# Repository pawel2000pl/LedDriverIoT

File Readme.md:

# IOT RGB Led driver

Project was designed for XIAO ESP32C3 and Waveshare ESP32C3-Zero.<br>
Compilable with Arduino and ESP-IDF.

## Example hardware application

## Screenshots

### Mobile

### Landscape (for computers)

### No-script (for bricks)

### Favorites

### Confguration

### Everything available also in dark-mode (auto detect)

## How to use a docker container
```
docker build -t led_driver_idf -f Idf.Dockerfile . && docker run -it -p 8000:8000 led_driver_idf
# or
# docker build -t led_driver_arduino -f Arduino.Dockerfile . && docker run -it -p 8000:8000 led_driver_arduino
```
then open http://0.0.0.0:8000 in your browser and download a binary file.

You can aslo run a script which builds the image, runs the container, downloads this file automatically and removes the container:
```
./compile_with_docker.sh
```

The file `iot-led-driver.bin` can be uploaded on `Configuration` page in `Update` tab.

## How to compile without a docker container

#### For all compilations
Before the compilation, it is required to compile resources to `.cpp` and `.h` files. It is also required after any modification of any file in the `resources` directory.
To compile resources, execute in the project directory:
~~~
python3 ./compilation_utils/compile_resources.py
~~~

#### For idf:
On the first usage of microcontroller you should run `idf.py erase_flash` to ensure that flash partitions will be initialized properly.<br>
Run `idf.py build` in the project directory.

#### For Arduino:
Open the file `main/main.ino` in Arduino. Set the following parameters:
* board: ESP32C3 - Dev module (requires additional installation)
* CPU Frequency: 160MHz (default)
* Flash size: 4MB
* Partition scheme: Minimal SPIFFS (1.9MB APP with OTA / 190kB SPIFFS)

## Runtime statistics
The runtime statistics are available on `/statistics.txt` endpoint.<br>
The last system statistics:
~~~
=== Tasks info ===
Name             |        Ticks | CPU % | Free stack |  Stack ptr
-----------------+--------------+-------+------------+------------
IDLE             |    390961538 |   85% |       1240 | 0x3fca6ef8
loopTask         |     34119316 |    7% |       3992 | 0x3fca87a8
knobs            |     20251982 |    4% |       1488 | 0x3fcb55d0
wifi             |      2405020 |    0% |       2128 | 0x3fcaedb0
tiT              |      1366588 |    0% |       2744 | 0x3fcaad80
animations       |       790686 |    0% |       1568 | 0x3fcb68a0
esp_timer        |       786223 |    0% |       3672 | 0x3fca4be8
shutdown         |       472535 |    0% |       1720 | 0x3fcb5f38
sys_evt          |         8169 |    0% |       2152 | 0x3fcac204
mdns             |         5225 |    0% |       3116 | 0x3fcb0fe4
arduino_events   |         4456 |    0% |       2836 | 0x3fcad03c
Tmr Svc          |            8 |    0% |       1792 | 0x3fca7660

=== Heap info ===
Total size:             247524
Minimum free heap:      111860  ( 45% )
Total free bytes:       155624  ( 62% )
Total allocated bytes:   91900  ( 37% )
Largest free block:     114688  ( 46% )
Blocks free:                10
Blocks allocated:          405
~~~

## How to connect for the first time

* Scan networks and find network with SSID `LedDriver` and connect to them with `ledDriver` password. Then type in browser `http://192.168.1.1`.
* If you do not see any network with SSID `LedDriver`, create it (as a Hotspot) on your phone with password `ledDriver` and restart the driver. The Hotspot must work with WiFi 5 or an older version.

Unfortunately, there is no way to predetermine driver's IP address in a network other than its own AccessPoint. <br>
The driver supports mDNS technology. After connecting to your network, try to enter the driver's hostname with suffix `.local` (f.e.: `http://led-driver.local`) in an address bar of a browser. Sometimes this technology requires a while to be detected by other devices in the network.<br>
In case of using `https` protocol you may be warned about danger of self signed or untrusted certificate.
Skip it and/or add this certificate to exceptions. 

## Hardware

### How it works

Select one of four possible configurations:
* Multiplexer #1
* Multiplexer #2
* Multiplexer #3
* simple #1
* simple #2
* unconnected

Each configuration might be modified by disconnecting potentiometers or removing thermistors.
The software matches pins automatically.

### Table with led driver pinout

...and possible hardware configurations

Pin|Name|XIAO|Waveshare|Multiplexer #1|Multiplexer #2|Multiplexer #3|Simple #1|Simple1 #2|Comment
---|----|----|---------|--------------|--------------|--------------|--------------|----------------|-------
1|LNA_IN|ANT|ANT|ANT|ANT|ANT|ANT|ANT|
2|VDD3P3|VCC 3,3|VCC 3,3|VCC 3,3|VCC 3,3|VCC 3,3|VCC 3,3|VCC 3,3|
3|VDD3P3|VCC 3,3|VCC 3,3||||||
4|XTAL_32K_P|internal|GP0||||||Cannot be connected during the booting (H/Z)
5|XTAL_32K_N|internal|GP1||||||Cannot be connected during the booting (H/Z)
6|GPIO2|D0|GP2|Mult COM|Mult COM|Mult COM|Potentiometer 0|Potentiometer 0|
7||EN|EN||||||
8|GPIO3|D1|GP3|H/Z|GND|UP|Potentiometer 1|Potentiometer 1|
9|MTMS|D2|GP4|FAN|FAN|FAN|Potentiometer 2|Potentiometer 2|
10|MTDI|D3|GP5|FLASH RST|FLASH RST|FLASH RST|FLASH RST|LED OUT 0|
11|VDD3P3_RTC|VCC 3,3|VCC 3,3||||||
12|MTCK|D4|GP6|Mult. SEL0|Mult. SEL0|Mult. SEL0|FAN (short them all)|LED OUT 1|
13|MTDO|D5|GP7|Mult. SEL1|Mult. SEL1|Mult. SEL1|FAN (short them all)|LED OUT 2|
14|GPIO8|D8|GP8|LED OUT 1|LED OUT 1|LED OUT 1|LED OUT 1|LED OUT 3|
15|GPIO9|D9|GP9|LED OUT 2|LED OUT 2|LED OUT 2|LED OUT 2|FLASH RST|Pulled-up during the booting (internal)
16|GPIO10|D10|GP10|LED OUT 3|LED OUT 3|LED OUT 3|LED OUT 3|FAN (short them all)|
17|VDD3P3_CPU|VCC 3,3|VCC 3,3||||||
18|VDD_SPI|VDD SPI|VDD SPI||||||
19|SPIHD|internal|internal||||||
20|SPIWP|internal|internal||||||
21|SPICS0|internal|internal||||||
22|SPICLK|internal|internal||||||
23|SPID|internal|internal||||||
24|SPIQ|internal|internal||||||
25|GPIO18|internal|ESP_USB_DP||||||
26|GPIO19|internal|ESP_USB_DM||||||
27|U0RXD|D7|GP20|LED OUT 0|LED OUT 0|LED OUT 0|LED OUT 0||
28|U0TXD|D6|GP21|Mult. SEL2|Mult. SEL2|Mult. SEL2|FAN (short them all)|FAN (short them all)|
29|XTAL_N|internal|internal||||||
30|XTAL_P|internal|internal||||||
31|VDDA|internal|internal||||||
32|VDDA|internal|internal||||||
33|GND|GND|GND||||||
Mult. Ch0||||Thermistor 0|Potentiometer 0|Thermistor 0|||
Mult. Ch1||||Thermistor 1|Potentiometer 1|Thermistor 1|||
Mult. Ch2||||Thermistor 2|Potentiometer 2|Thermistor 2|||
Mult. Ch3||||Thermistor 3|Potentiometer 3|Thermistor 3|||
Mult. Ch4||||Potentiometer 0|||||
Mult. Ch5||||Potentiometer 1|||||
Mult. Ch6||||Potentiometer 2|||||
Mult. Ch7||||Potentiometer 3|||||

### XIAO ESP32C3 board pinout - cheat sheet

### Waveshare ESP32C3-Zero board pinout - cheat sheet

### ESP32-C3 VROOM V2 pinout - cheat sheet

### ESP32-C3 pinout - cheat sheet

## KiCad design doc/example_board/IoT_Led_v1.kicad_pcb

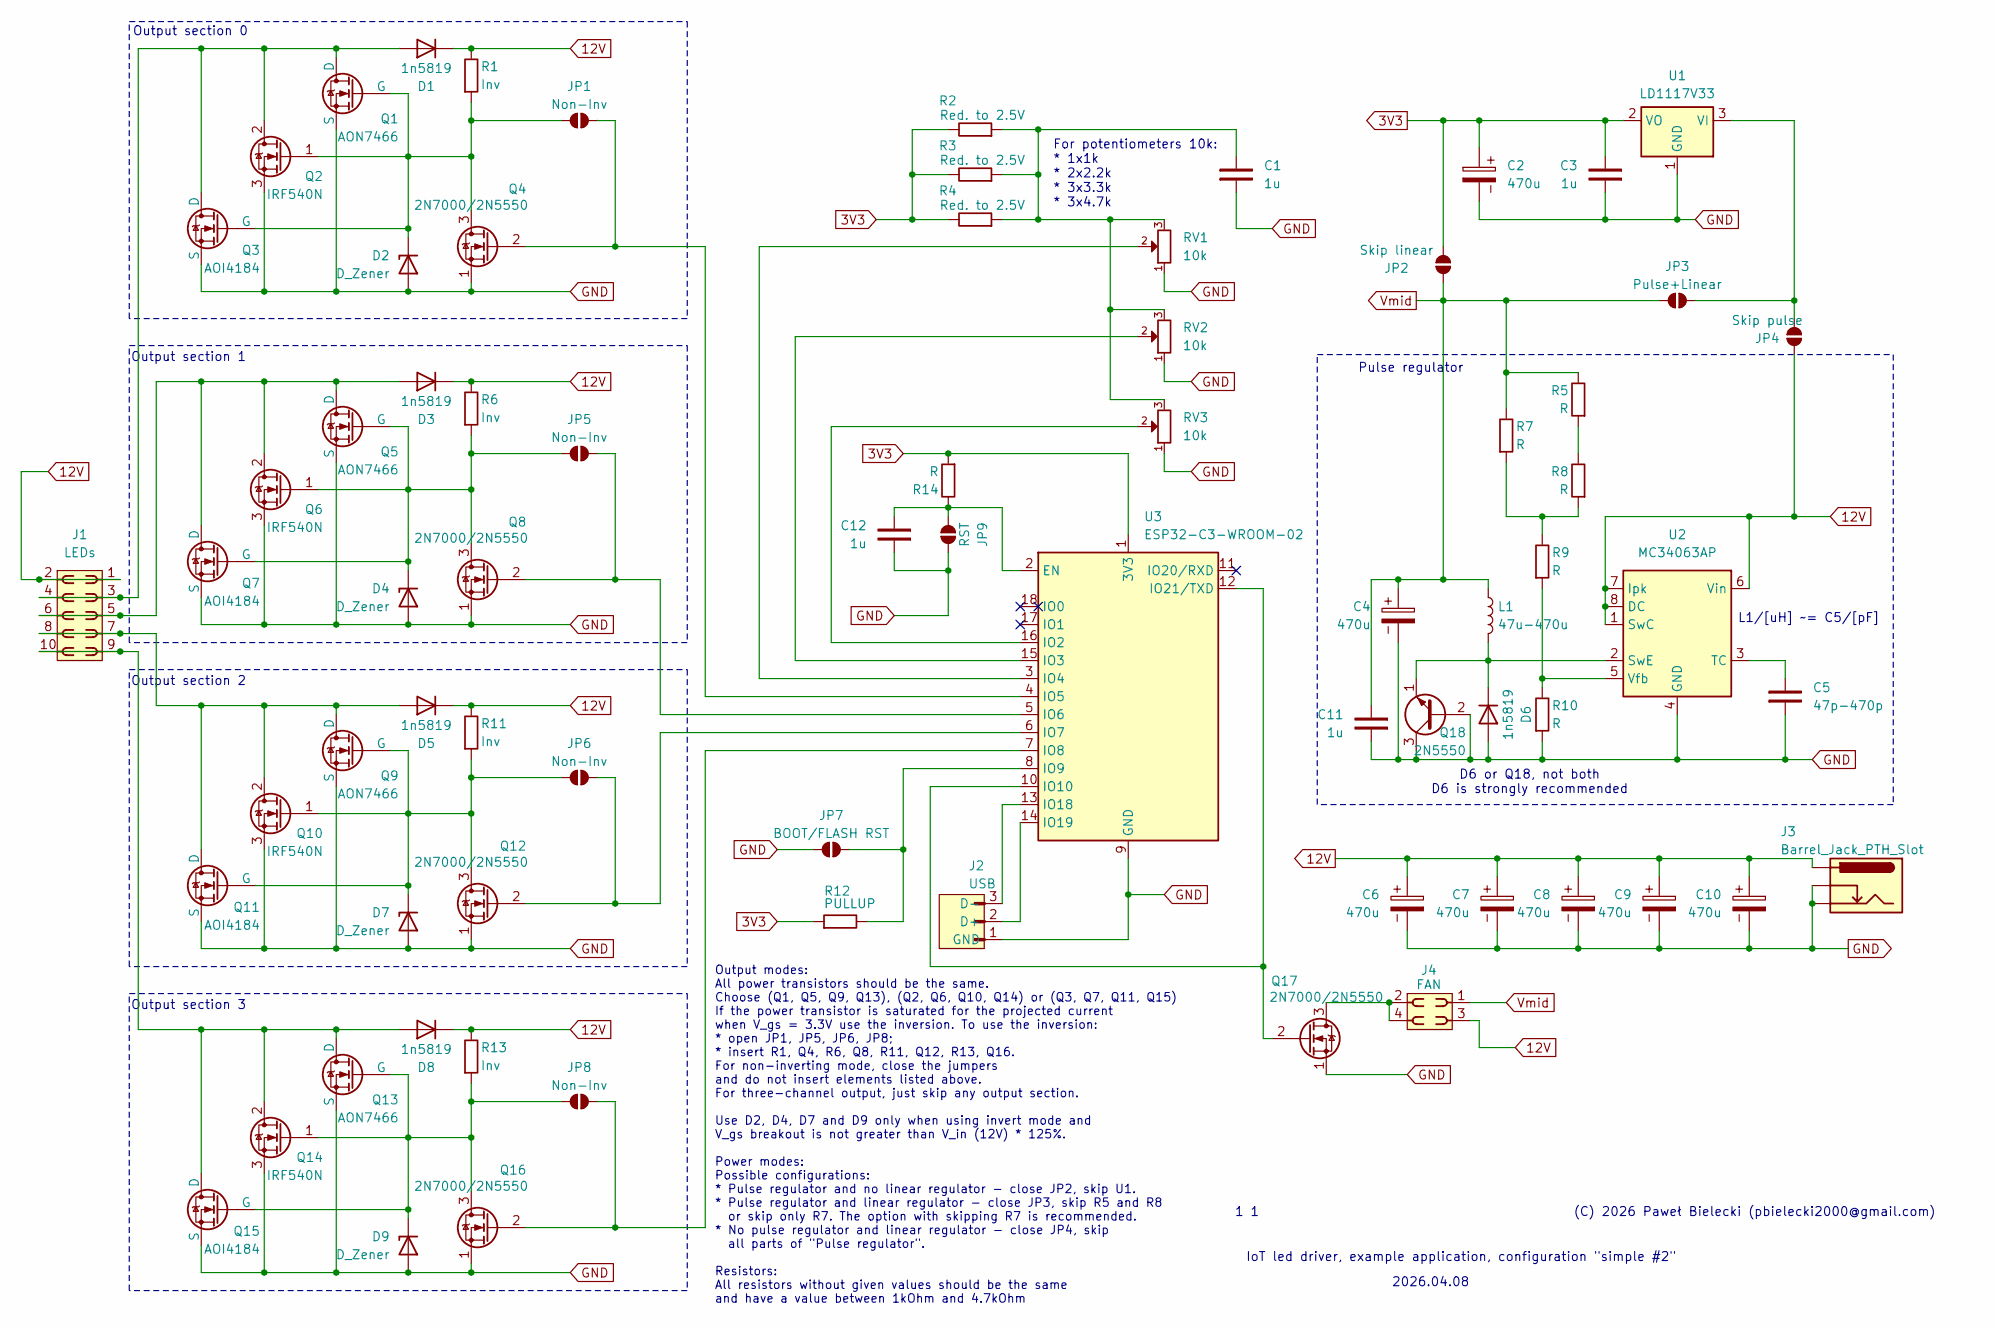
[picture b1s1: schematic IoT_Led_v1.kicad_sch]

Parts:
C1, C3, C11, C12: 1u; C_Disc_D3.0mm_W2.0mm_P2.50mm
C2, C4, C6, C7, C8, C9, C10: 470u; CP_Radial_D5.0mm_P2.50mm
C5: 47p-470p; C_Disc_D3.0mm_W2.0mm_P2.50mm
D1, D3, D5, D6, D8: 1n5819; D_DO-41_SOD81_P10.16mm_Horizontal
D2, D4, D7, D9: D_Zener; D_DO-41_SOD81_P10.16mm_Horizontal
J1: LEDs; PinSocket_2x05_P2.54mm_Vertical
J2: USB; PinHeader_1x03_P2.54mm_Vertical
J3: Barrel_Jack_PTH_Slot
J4: FAN; PinSocket_2x02_P2.54mm_Vertical
JP1, JP5, JP6, JP8: Non-Inv; Jumper_2_NO_NoSilk
JP2: Skip linear; Jumper_2_NO_NoSilk
JP3: Pulse+Linear; Jumper_2_NO_NoSilk
JP4: Skip pulse; Jumper_2_NO_NoSilk
JP7: BOOT/FLASH RST; Jumper_2_NO_NoSilk
JP9: RST; Jumper_2_NO_NoSilk
L1: 47u-470u; L_Axial_L5.3mm_D2.2mm_P2.54mm_Vertical_Vishay_IM-1
Q1, Q5, Q9, Q13: AON7466
Q2, Q6, Q10, Q14: IRF540N; TO-220-3_Vertical
Q3, Q7, Q11, Q15: AOI4184; TO-251-3_Vertical
Q4, Q8, Q12, Q16, Q17: 2N7000/2N5550; TO-92_Inline
Q18: 2N5550; TO-92_Inline
R1, R6, R11, R13: Inv; R_Axial_DIN0207_L6.3mm_D2.5mm_P10.16mm_Horizontal
R2, R3, R4: Red. to 2.5V; R_Axial_DIN0207_L6.3mm_D2.5mm_P10.16mm_Horizontal
R5, R7, R8, R9, R10, R14: R; R_Axial_DIN0207_L6.3mm_D2.5mm_P10.16mm_Horizontal
R12: PULLUP; R_Axial_DIN0207_L6.3mm_D2.5mm_P10.16mm_Horizontal
RV1, RV2, RV3: 10k; Potentiometer_Alps_RK163_Single_Horizontal
U1: LD1117V33; TO-220-3_Vertical
U2: MC34063AP; DIP-8_W7.62mm
U3: ESP32-C3-WROOM-02

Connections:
3V3: C2.1, C3.2, JP2.1 (A), R2.2, R3.2, R4.2, R12.1, R14.1, U1.2 (VO), U3.1 (3V3)
12V: C6.1, C7.1, C8.1, C9.1, C10.1, D1.1 (K), D3.1 (K), D5.1 (K), D8.1 (K), J1.1, J1.2, J3.PWR, J4.3, JP4.2 (B), R1.2, R6.2, R11.2, R13.2, U2.1 (SwC), U2.6 (Vin), U2.7 (Ipk), U2.8 (DC)
GND: C1.1, C2.2, C3.1, C4.2, C5.1, C6.2, C7.2, C8.2, C9.2, C10.2, C11.1, C12.1, D2.2 (A), D4.2 (A), D6.2 (A), D7.2 (A), D9.2 (A), J2.1 (GND), J3.GND, J3.GNDBREAK, JP7.1 (A), JP9.2 (B), Q1.3 (S), Q2.3 (S), Q3.3 (S), Q4.1 (S), Q5.3 (S), Q6.3 (S), Q7.3 (S), Q8.1 (S), Q9.3 (S), Q10.3 (S), Q11.3 (S), Q12.1 (S), Q13.3 (S), Q14.3 (S), Q15.3 (S), Q16.1 (S), Q17.1 (S), Q18.2 (B), Q18.3 (C), R10.1, RV1.1, RV2.1, RV3.1, U1.1 (GND), U2.4 (GND), U3.9 (GND), U3.19 (GND)
unnamed: C1.2, R2.1, R3.1, R4.1, RV1.3, RV2.3, RV3.3
unnamed: D1.2 (A), J1.3, J1.4, Q1.1 (D), Q2.2 (D), Q3.2 (D)
unnamed: D2.1 (K), JP1.2 (B), Q1.2 (G), Q2.1 (G), Q3.1 (G), Q4.3 (D), R1.1
unnamed: D3.2 (A), J1.5, J1.6, Q5.1 (D), Q6.2 (D), Q7.2 (D)
unnamed: D4.1 (K), JP5.2 (B), Q5.2 (G), Q6.1 (G), Q7.1 (G), Q8.3 (D), R6.1
unnamed: D5.2 (A), J1.7, J1.8, Q9.1 (D), Q10.2 (D), Q11.2 (D)
unnamed: D6.1 (K), L1.2, Q18.1 (E), U2.2 (SwE)
unnamed: D7.1 (K), JP6.2 (B), Q9.2 (G), Q10.1 (G), Q11.1 (G), Q12.3 (D), R11.1
unnamed: D8.2 (A), J1.9, J1.10, Q13.1 (D), Q14.2 (D), Q15.2 (D)
unnamed: D9.1 (K), JP8.2 (B), Q13.2 (G), Q14.1 (G), Q15.1 (G), Q16.3 (D), R13.1
unnamed: J2.2 (D+), U3.14 (IO19)
unnamed: J2.3 (D-), U3.13 (IO18)
unnamed: JP1.1 (A), Q4.2 (G), U3.4 (IO5)
unnamed: JP3.1 (A), JP4.1 (A), U1.3 (VI)
unnamed: JP5.1 (A), Q8.2 (G), U3.5 (IO6)
unnamed: JP6.1 (A), Q12.2 (G), U3.6 (IO7)
unnamed: JP7.2 (B), R12.2, U3.8 (IO9)
unnamed: JP8.1 (A), Q16.2 (G), U3.7 (IO8)
unnamed: C12.2, JP9.1 (A), R14.2, U3.2 (EN)
unnamed: J4.2, J4.4, Q17.3 (D)
unnamed: Q17.2 (G), U3.10 (IO10), U3.12 (IO21/TXD)
unnamed: R5.1, R8.2
unnamed: R7.1, R8.1, R9.2
unnamed: C5.2, U2.3 (TC)
unnamed: R9.1, R10.2, U2.5 (Vfb)
unnamed: RV3.2, U3.16 (IO2)
unnamed: RV2.2, U3.15 (IO3)
unnamed: RV1.2, U3.3 (IO4)
Vmid: C4.1, C11.2, J4.1, JP2.2 (B), JP3.2 (B), L1.1, R5.2, R7.2

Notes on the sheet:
L1/[uH] ~= C5/[pF]
2026.04.08
IoT led driver, example application, configuration "simple #2"
Output section 0
Pulse regulator
Output section 3
1 1
(C) 2026 Paweł Bielecki (pbielecki2000@gmail.com)
Output modes: All power transistors should be the same. Choose (Q1, Q5, Q9, Q13), (Q2, Q6, Q10, Q14) or (Q3, Q7, Q11, Q15) If the power transistor is saturated for the projected current when V_gs = 3.3V use the inversion. To use the inversion: * open JP1, JP5, JP6, JP8; * insert R1, Q4, R6, Q8, R11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
D6 or Q18, not both D6 is strongly recommended
For potentiometers 10k: * 1x1k * 2x2.2k * 3x3.3k * 3x4.7k
Output section 1
Output section 2

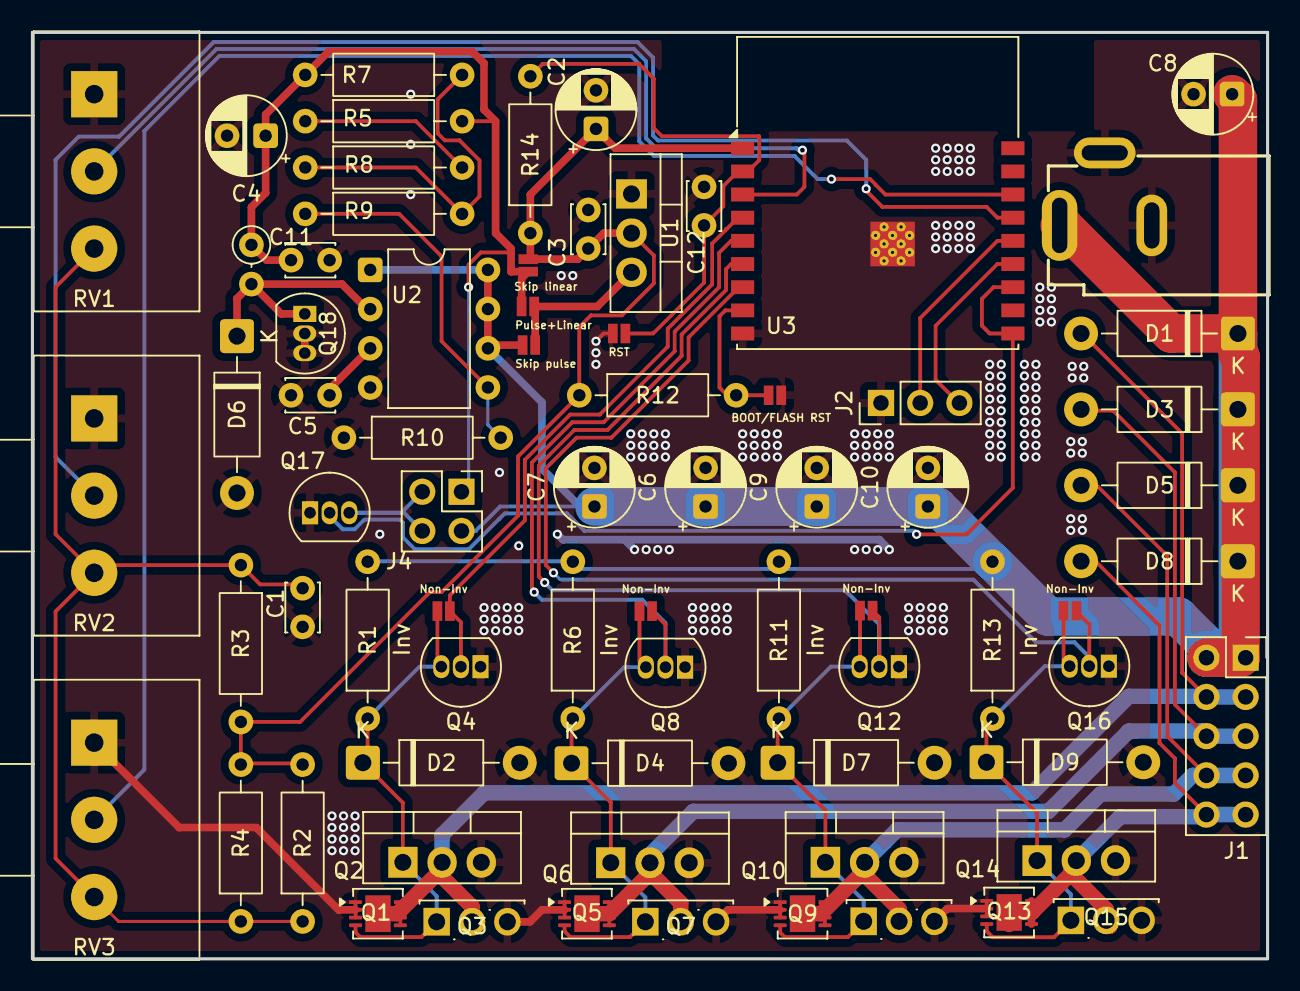
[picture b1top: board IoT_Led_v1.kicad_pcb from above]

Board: 2 copper layers, 80.0 x 60.0 mm, 73 parts (0 on the bottom side), 32 nets.

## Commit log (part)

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2024-04-24 Frontend of hardware configuration
2024-04-30 Implemented interface for configuration through wifi
2024-05-01 Added configuration loading and wifi-configuration to micronotroller code
2024-05-01 Added "use strict". Implemented conversion functions in C++. Changed Knob to DOM component.
2024-05-02 Knobs optimalization. Configuration validation, loading and saving.
2024-05-05 Fixed storing configuration
2024-05-06 Connected WiFi color settings.
2024-05-07 Removed bluetooth & whitelists. Added some wifi config.
2024-05-07 Finished WiFi features
2024-05-07 Added input function filtering to WiFi
2024-05-08 Added functions for filtering outputs
2024-05-08 Formatted code
2024-05-08 Networks with hidden SSID
2024-05-09 Moved input filtering to server
2024-05-10 Code optimalization
2024-05-10 Added simple mode
2024-05-11 Added outputs. Added reading analog inputs. Added pin (button) for resetting configuration.
2024-05-11 Added better apperance for landscape orientations
2024-05-11 Math function builders optimalization, interface changes (responsiveness).
2024-05-12 Added Readme
2024-05-12 Diagram update
2024-05-12 Yet another diagram update
2024-05-12 Changed positions of configuration settings, updated example application (readme)
2024-05-14 Added condition checking if knobs can be used.
2024-05-15 Remved some warnings.
2024-05-15 Interfrating with idf
2024-05-15 Added software updates
2024-05-15 Json keys restoration.
2024-05-15 Added OTA server with automatic building for updates.
2024-05-15 Added more published build files to server. Added proper partitions. Added checksums and timestamp to server files.
2024-05-15 Added main page for server
2024-05-16 Fixed build container
2024-05-24 Trials of implementing one line input
2024-05-25 Added full support for multiplexer
2024-05-25 Added hardware detection (for one software for all types)
2024-05-25 Bug fixes after test of knobs (multiplexer or not etc)
2024-05-25 Readme update
2024-05-25 Added ground to thermistors
2024-05-26 Added knobs noises reduction to user configuration
2024-05-26 Inverted noises reduction value
2024-05-27 Fixed colors validation
2024-05-27 Fixed flickering at 330Hz. Added delay for gate charging to minimal value.
2024-09-28 Styles update - optimized for high screens
2024-09-29 Repaired ns_error_net_reset
2024-09-30 Added favorites colors
2024-09-30 Wifi settings protection on changes
2024-10-01 Bug fixes, added cache headers
2024-10-01 Repaired bias configuration. Fixed example application: max analog voltage is 2.5V. Added default "favorite" colors.
2024-10-01 Added pageshow and visibilitychange events
2024-10-04 Huge code refactorization. Improvment: when color is changed to black, hue and saturation does not reset.
2024-10-04 Version checking & invalidating cache when it change
2024-10-05 Code format. Refactorisation: created separate knob module
2024-10-05 Code refactoring: WiFi
2024-10-05 Added description for hardware settings
2024-10-05 Repaired real-time configuration applying
2024-10-05 Changed indent to tabs
2024-10-06 Changed frequency settings
2024-10-06 Updated screenshot
2024-10-08 Added scalling to output channels to tailor led strips for true colors.
2024-10-09 Added phase control
2024-10-09 Changed splitting phase mode. Added separate mode for splitting with white.
2024-10-10 Phases refactorization. Fixed error with white channel in eco mode.
2024-10-10 Changed favicon
2024-10-10 Refactorization. Fixed problems with saturation on RGB mode. Added statisticts to compilation script
2024-10-12 Added rare checks interval
2024-10-12 Added knob checking with timer. Added random cache max-age.
2024-10-13 Updated default configuration to match with Readme and typical application
2024-10-13 Added description for WiFi channel selection
2024-10-18 Added middle-click event to menu buttons. Changed knob (read) frequency to 60Hz.
2024-10-20 Fixed menu touching
2024-10-20 Added compability with ESP32-C3-Zero (Waveshare)
2024-10-21 Fixed compability with esp32c3-zero
2024-10-21 Added library for SPI with DMA
2024-10-21 Removed columns from documentation. Updated gitignore & dockerignore
2024-10-21 Removed controllin onboard led on Waveshare esp32c3-zero
2024-10-21 Optimalization: removed unused include
2024-10-21 Draft of generating spi buffer
2024-10-22 Calculated timings for ws* protocols
2024-10-24 Optimized finishing addressed buffer
2024-10-24 Reorganized deploy files
2024-10-24 Refactorization of configuration
2024-10-24 Added resources version
2024-10-27 Fixed initialization sequence
2024-10-30 Added classes for configuration
2024-10-30 Added installation of (working) https server library
2024-11-02 Changed library. Made the code compilable again
2024-11-02 Repaired code that it works
2024-11-03 Removed unused library
2024-11-03 Files reorganization 1
2024-11-03 Files reorganization 2
2024-11-03 Removed compiled resources
2024-11-03 Storing certificates in SPIFFS
2024-11-06 Added additional actions like removing cert, restart or running connection pipeline
2024-11-07 Fixed function (order) execution. Udated version number.
2024-11-07 Moved files to new location Added missing semicolon.
2024-11-09 Updated doc for future works
2024-11-09 Added temperature endpoint
2024-11-13 Added (working) mDNS. Added clearing cache by redirecting to another page
2024-11-13 Updated wifi description
2024-11-16 Added function for filling addressed led sections
2024-11-17 Added cleaning memory after reconnecting mDNS
2024-12-14 Added ETag support
2024-12-18 Added checking config version on boot. Added setting for captive portal.
2024-12-18 Settings channel limits from current set
2024-12-18 Changed server pipeline
2024-12-29 Added lock of knobs when saving settings
2024-12-29 Added RequestReader
2024-12-29 Reading depended on content length and free memory
2024-12-29 Refactored class RequestReader (splitted to definition and implementation)
2024-12-29 Minor changes: changed update information, removed unused variable, added casting to remove warnings
2024-12-30 Fixed testing for string in json validator
2024-12-30 Added ResponseWriter
2024-12-30 Loading file content to dynamic vector. Fixed build script
2025-01-01 Fixed json validation. Added tests for configuration.
2025-01-01 Added enabling colors. Fixed "enble" misspell. Fixed upgrading client app.
2025-01-02 Reduced memory usage on some request
2025-01-02 Fixed a typo
2025-01-03 Version in localStorage is now only resource hash
2025-01-03 Fixed flickering when turning off leds channel.
2025-01-25 Fixes for bugs in ESP32DMASPIMaster
2025-04-28 Set downloading timeout to infinity
2025-04-28 Added thermic protection
2025-04-29 Added fixed point arithmetic
2025-04-29 Updated fixed_point library
2025-05-01 Updated (fixed) taylormath
2025-05-02 Unified converter of fixedpoint to arduino json
2025-05-02 Decreased size of using fixedpoint
2025-05-02 Updated fixedpoint: repairet math on another signed integers
2025-05-02 Fixed changes. Works almost good.
2025-05-03 Increased resolution to fixed64
2025-05-03 updated taylormath
2025-05-03 Added additional checks (searchers) for update success
2025-05-03 Fixed simple mode
2025-05-04 Changed names from "float" to "fixed". Updated endpoints to works with fixedpoints
2025-05-04 Added let in utils.js
2025-05-04 Taylored variables accuracy
2025-05-05 Updatesof fixedpoint and taylormath
2025-05-14 Updated math libraries
2025-09-11 Updated parameters for initialization
2025-10-04 Fixed overwriting settings if saved before loaded. Added multiple trials for mounting SPIFFS. Added rewriting filesystem in case of error.
2025-10-04 Optimized fixedpoint
2025-10-05 Fixed fixedpoint and conversions
2025-10-06 Moved fading out to "output" module. Added simple lock for timer. Added additional information for printing by compile_resources.py script.
2025-11-11 Updated fixedpoint lib
2025-11-14 Added configuration specialized for boards
2025-11-18 Downloaded ArduinoJson and esp32_https_server
2025-11-18 Updated idf-build (to master)
2025-11-18 Some progress with compilation
2025-11-19 Made it compile and work
2025-11-23 Normalized tasks
2025-11-23 Renamed files
2025-11-25 Removed git directory from IDF container
2025-11-26 Moved lib files to lib directory, Removed depedencies.lock from repo, Added polyapprox
2025-11-26 Reduced logs on IDF
2025-11-27 Updated polyapprox
2025-11-27 Confirmation before leaving after modyfying and not saving settings.
2025-11-29 Created module for animations. Changed random source to true ranom generator.
2025-11-29 Fixed initializing transition
2025-11-29 Removed "extern" in definitions of etag in resources.
2025-11-29 Fixed simple mode; Normalized html files. Added question before leaving favorites after modification without saving.
2025-11-30 Non-blocking delay when reading analogs.
2025-11-30 Added statistics endpoint
2025-12-01 Unified menu. Marked passwords for wifi as text to avoid saving in browser. Added font for password inputs.
2025-12-01 Added license to the font
2025-12-04 Added template for creating animations
2025-12-07 Added endpoint for playing animations without saving.
2025-12-07 More frontend updates: added labels and controls (templates)
2025-12-07 Fixed compilation of binary resources
2025-12-10 Added function for listing all inputs by name
2025-12-12 Added saving and loading stages
2025-12-15 Added savings and loading for stages. Oprimized json serialization.
2025-12-17 Modified usage of ArduinoJson (removed references for JsonVariant). Refactored functions for loading and saving jsons on frontend. Added utils functions for animations.
2025-12-23 Make it work (integration)
2026-03-27 Updated *ignore. Fixed compile resources for binary files
2026-03-28 Added default animations. Added prevention from suing clipboard when no https
2026-03-28 Fixed problems with sending (large) resources through https
2026-03-28 Added global animation lightness
2026-03-28 Removed resource compression
2026-03-29 Memory optimalization
2026-03-29 Fixed error with global animation lightness when no randomness
2026-03-30 Added default animations
2026-03-30 Changed animations fps to 120. Minor frontend fixes
2026-03-30 Added exporting a single animation
2026-04-02 Enchanced knobs amortisation. Changed name of fixed32_f to fixed64_f
2026-04-04 Added class nd endpoint for 1kB of logs. Added flags for servers state. Fixed WiFi behaviour after disconnecting AP when built with idf. Added flag for checking if there was any query (instead of tim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
2026-04-05 Updated efault animations
2026-04-05 Changed classes for hardware configurations
2026-04-06 Files rearranged
2026-04-06 Fixed inplace vector. Updated sdkconfig.
2026-04-06 Hope that fixed
2026-04-07 Added unonnected configuration
2026-04-07 Fixed importing configuration
2026-04-07 Simplify functions for checking pin connections
2026-04-08 Changed recursive <p> to <div>s
2026-04-08 Added example KiCad project
2026-04-08 Updated license and polyapprox lib
2026-04-08 Updated readme, added cheatsheet for esp32c3-vroom-v2
2026-04-09 Upgrading the example board
2026-04-11 Added settings default animations by the name
2026-04-11 Moved fetching animations to config-specific script
2026-04-11 Fixed HTTP library
2026-04-11 Inreased connection pool, upgraded http lib
2026-04-11 Updated default filters
2026-04-11 Added Littlefs with conversion from SPIFFS
2026-04-11 Removed unused libraries from Arduino Docker container
2026-04-11 Fixed logs
2026-04-12 Code refactor, version upgrade
2026-04-14 Added checking if the file was saved
2026-04-19 Fixed detecting the hardware configuration. Removed rewritting the configuration on every startup.
2026-04-20 Added moving buttons for moving animations (up/down)
2026-04-20 Fixed styles in animations
2026-04-20 Fixed buttons up&down in animations.
2026-04-22 Code format
2026-04-23 Changing animations hue, saturation and value with the main control.
2026-04-24 Fixes: removed rests of animation lightness, added values normalization in some places. Optimized hue-zero functionality.
2026-04-26 Set apPeriodicScan = false when the sta priority list is empty
2026-04-26 Changed std::vector to std::array in constants list in wifi module.
2026-04-27 Optimalization
2026-04-27 Fixed default animations settings. Fixed default black animation.
